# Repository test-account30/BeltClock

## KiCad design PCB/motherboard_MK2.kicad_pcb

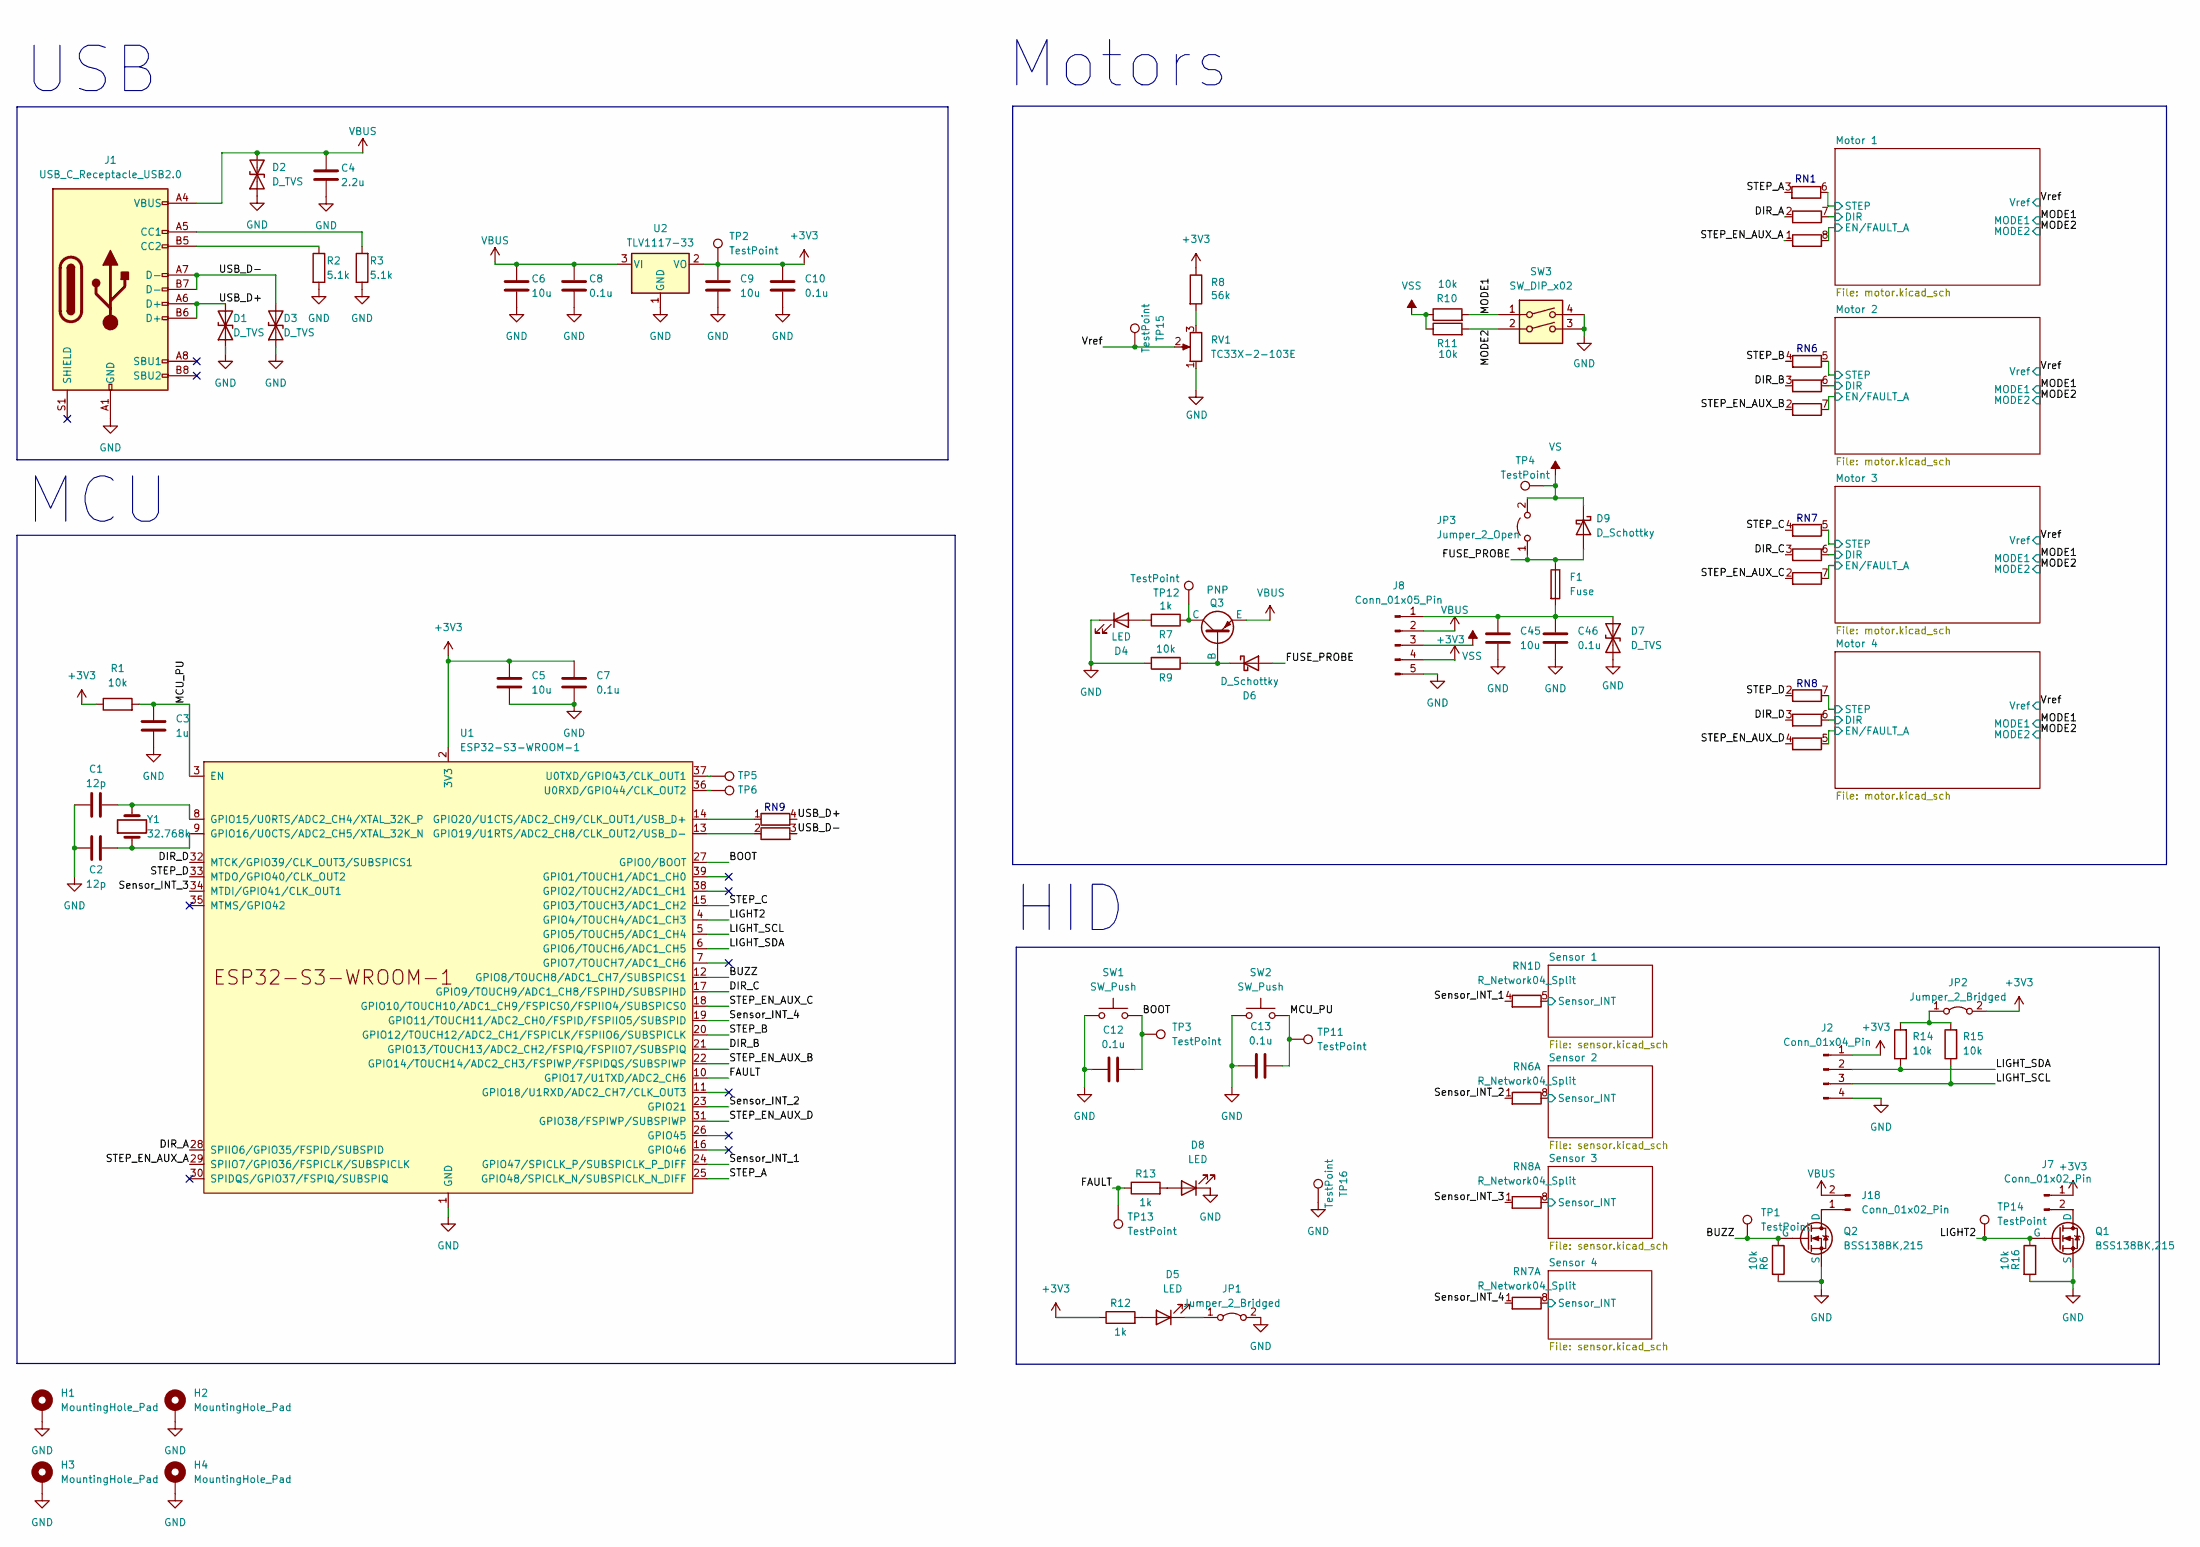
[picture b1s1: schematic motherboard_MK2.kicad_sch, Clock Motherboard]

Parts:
C1, C2: 12p; C_0603_1608Metric; Part Number VJ0805A120FXJCW1BC
C3: 1u; C_0603_1608Metric; Part Number CL10A105KO8NNNC
C4: 2.2u; C_0603_1608Metric; Part Number CL10A225KO8NNNC
C5, C6, C9, C45: 10u; C_1206_3216Metric; Part Number C1206C106K4PACTU
C7, C8, C10, C12, C13, C46: 0.1u; C_0603_1608Metric; Part Number CL10B104KO8NNNC
D1, D3: D_TVS; D_SOD-882; Part Number SP3021-01ETG
D2, D7: D_TVS; ZDO_SOD723_LTF-L; Part Number SP1003-01DTG
D4, D5, D8: LED; LED_0805_2012Metric; Part Number MCL-S270YC
D6: D_Schottky; D_SOD-523; Part Number RB540SM-40FHT2R
D9: D_Schottky; Nexperia_CFP3_SOD-123W; Part Number PMEG4030EXEX
F1: Fuse; Fuse_1206_3216Metric; Part Number F1206FA3000V032TM
H1, H2, H3, H4: MountingHole_Pad; MountingHole_3.2mm_M3; Part Number N/A
J1: USB_C_Receptacle_USB2.0; USB4120-03-C_GCT; Part Number USB4120-03-C
J2: Conn_01x04_Pin; Molex_PicoBlade_53048-0410_1x04_P1.25mm_Horizontal; Part Number 53048-0410
J7: Conn_01x02_Pin; Molex_PicoBlade_53048-0210_1x02_P1.25mm_Horizontal; Part Number 53047-0210
J8: Conn_01x05_Pin; PinHeader_1x05_P2.54mm_Vertical; Part Number generic
J18: Conn_01x02_Pin; Molex_PicoBlade_53047-0210_1x02_P1.25mm_Vertical; Part Number 53047-0210
JP1, JP2: Jumper_2_Bridged; SolderJumper-2_P1.3mm_Bridged2Bar_Pad1.0x1.5mm; Part Number N/A
JP3: Jumper_2_Open; SolderJumper-2_P1.3mm_Open_Pad1.0x1.5mm; Part Number N/A
Q1, Q2: BSS138BK,215; SOT-23; Part Number BSS138BK,215
Q3: PNP; SOT-23; Part Number DSS5240T-7
R1, R6, R10, R11, R14, R15, R16: 10k; R_0603_1608Metric; Part Number MR06X1002FTLV
R2, R3: 5.1k; R_0603_1608Metric; Tolerance 1%; Part Number MCWR06X5101FTL
R7, R12, R13: 1k; R_0805_2012Metric; Tolerence 10%; Part Number MCWR08X1001FTL
R8: 56k; R_0603_1608Metric; Part Number MR06X563 JTLV
R9: 10k; R_0603_1608Metric; Tolerence 10%; Part Number MR06X1002FTLV
RN1, RN6, RN7, RN8: R_Network04_Split; R_Array_Convex_4x0402; Part Number MCPNF42JT-YR0R0
RN9: R_Pack02_Split; R_Array_Convex_2x0402; Part Number MCPNF22JT-YR0R0
RV1: TC33X-2-103E; Potentiometer_Bourns_TC33X_Vertical; Part Number TC33X-2-103E
SW1, SW2: SW_Push; SW_SPST_TL3305A; Part Number TL3305AF160QG.
SW3: SW_DIP_x02; DIP-4_W7.62mm; Part Number MCNDI-02S
TP1, TP3, TP11, TP12, TP13, TP14: TestPoint; TestPoint_Pad_D1.0mm; Part Number N/A
TP2, TP4, TP5, TP6, TP16: TestPoint; TestPoint_Pad_1.0x1.0mm; Part Number N/A
TP15: TestPoint; TestPoint_Pad_2.0x2.0mm; Part Number N/A
U1: ESP32-S3-WROOM-1; Part Number DFR0896
U2: TLV1117-33; SOT-223; Part Number LD1117S33CTR
Y1: 32.768k; Crystal_SMD_3215-2Pin_3.2x1.5mm; Part Number RT3215-32.768-12.5-TR-10PPM

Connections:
+3V3: C5.1, C7.1, C9.1, C10.1, J2.1, J7.1, J8.4, JP2.2 (B), R1.1, R8.1, R12.1, TP2.1, U1.2 (3V3), U2.2 (VO); also elsewhere on the board
/BOOT: C12.1, SW1.2, TP3.1, U1.27 (GPIO0/BOOT)
/BUZZ: Q2.2 (G), R6.1, TP1.1, U1.12 (GPIO8/TOUCH8/ADC1_CH7/SUBSPICS1)
/DIR_A: RN1.2, U1.28 (SPIIO6/GPIO35/FSPID/SUBSPID)
/DIR_B: RN6.3, U1.21 (GPIO13/TOUCH13/ADC2_CH2/FSPIQ/FSPIIO7/S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)
/DIR_C: RN7.3, U1.17 (GPIO9/TOUCH9/ADC1_CH8/FSPIHD/SUBSPIHD)
/DIR_D: RN8.3, U1.32 (MTCK/GPIO39/CLK_OUT3/SUBSPICS1)
/FAULT: R13.1, TP13.1, U1.10 (GPIO17/U1TXD/ADC2_CH6)
/FUSE_PROBE: D6.2 (A), D9.2 (A), F1.1, JP3.1 (A)
/LIGHT2: Q1.2 (G), R16.1, TP14.1, U1.4 (GPIO4/TOUCH4/ADC1_CH3)
/LIGHT_SCL: J2.3, R15.1, U1.5 (GPIO5/TOUCH5/ADC1_CH4)
/LIGHT_SDA: J2.2, R14.1, U1.6 (GPIO6/TOUCH6/ADC1_CH5)
/MCU_PU: C3.1, C13.1, R1.2, SW2.2, TP11.1, U1.3 (EN)
/MODE1: R10.2, SW3.1; also elsewhere on the board
/MODE2: R11.2, SW3.2; also elsewhere on the board
/Motor 1/DIR: RN1.7; also elsewhere on the board
/Motor 1/EN/FAULT: RN1.8; also elsewhere on the board
/Motor 1/STEP: RN1.6; also elsewhere on the board
/Motor 2/DIR: RN6.6; also elsewhere on the board
/Motor 2/EN/FAULT: RN6.7; also elsewhere on the board
/Motor 2/STEP: RN6.5; also elsewhere on the board
/Motor 3/DIR: RN7.6; also elsewhere on the board
/Motor 3/EN/FAULT: RN7.7; also elsewhere on the board
/Motor 3/STEP: RN7.5; also elsewhere on the board
/Motor 4/DIR: RN8.6; also elsewhere on the board
/Motor 4/EN/FAULT: RN8.5; also elsewhere on the board
/Motor 4/STEP: RN8.7; also elsewhere on the board
/STEP_A: RN1.3, U1.25 (GPIO48/SPICLK_N/SUBSPICLK_N_DIFF)
/STEP_B: RN6.4, U1.20 (GPIO12/TOUCH12/ADC2_CH1/FSPICLK/FSPIIO6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)
/STEP_C: RN7.4, U1.15 (GPIO3/TOUCH3/ADC1_CH2)
/STEP_D: RN8.2, U1.33 (MTDO/GPIO40/CLK_OUT2)
/STEP_EN_AUX_A: RN1.1, U1.29 (SPIIO7/GPIO36/FSPICLK/SUBSPICLK)
/STEP_EN_AUX_B: RN6.2, U1.22 (GPIO14/TOUCH14/ADC2_CH3/FSPIWP/FSPIDQS/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)
/STEP_EN_AUX_C: RN7.2, U1.18 (GPIO10/TOUCH10/ADC1_CH9/FSPICS0/FSPIIO4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)
/STEP_EN_AUX_D: RN8.4, U1.31 (GPIO38/FSPIWP/SUBSPIWP)
/Sensor 1/Sensor_INT: RN1.5; also elsewhere on the board
/Sensor 2/Sensor_INT: RN6.8; also elsewhere on the board
/Sensor 3/Sensor_INT: RN8.8; also elsewhere on the board
/Sensor 4/Sensor_INT: RN7.8; also elsewhere on the board
/Sensor_INT_1: RN1.4, U1.24 (GPIO47/SPICLK_P/SUBSPICLK_P_DIFF)
/Sensor_INT_2: RN6.1, U1.23 (GPIO21)
/Sensor_INT_3: RN8.1, U1.34 (MTDI/GPIO41/CLK_OUT1)
/Sensor_INT_4: RN7.1, U1.19 (GPIO11/TOUCH11/ADC2_CH0/FSPID/FSPIIO5/S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)
/USB_D+: D1.2 (A2), J1.A6 (D+), J1.B6 (D+), RN9.4 (R1.2)
/USB_D-: D3.2 (A2), J1.A7 (D-), J1.B7 (D-), RN9.3 (R2.2)
/Vref: RV1.2, TP15.1; also elsewhere on the board
GND: C1.1, C2.1, C3.2, C4.2, C5.2, C6.2, C7.2, C8.2, C9.2, C10.2, C12.2, C13.2, C45.2, C46.2, D1.1 (A1), D2.1 (A1), D3.1 (A1), D4.1 (K), D7.2 (A2), D8.1 (K), H1.1, H2.1, H3.1, H4.1, J1.A1 (GND), J1.A12 (GND), J1.B1 (GND), J1.B12 (GND), J2.4, J8.5, JP1.2 (B), Q1.3 (S), Q2.3 (S), R2.2, R3.1, R6.2, R9.2, R16.2, RV1.1, SW1.1, SW2.1, SW3.3, SW3.4, TP16.1, U1.1 (GND), U1.40 (GND), U1.41 (GND), U2.1 (GND); also elsewhere on the board
unnamed: D4.2 (A), R7.2
unnamed: D5.2 (A), R12.2
unnamed: D5.1 (K), JP1.1 (A)
unnamed: D6.1 (K), Q3.2 (B), R9.1
unnamed: C45.1, C46.1, D7.1 (A1), F1.2, J8.1
unnamed: D8.2 (A), R13.2
unnamed: J1.A5 (CC1), R3.2
unnamed: J1.B5 (CC2), R2.1
unnamed: J7.2, Q1.1 (D)
unnamed: J18.1, Q2.1 (D)
unnamed: JP2.1 (A), R14.2, R15.2
unnamed: Q3.1 (C), R7.1, TP12.1
unnamed: R8.2, RV1.3
unnamed: RN9.1 (R1.1), U1.14 (GPIO20/U1CTS/ADC2_CH9/CLK_OUT1/USB_D+)
unnamed: RN9.2 (R2.1), U1.13 (GPIO19/U1RTS/ADC2_CH8/CLK_OUT2/USB_D-)
unnamed: C1.2, U1.8 (GPIO15/U0RTS/ADC2_CH4/XTAL_32K_P), Y1.2
unnamed: C2.2, U1.9 (GPIO16/U0CTS/ADC2_CH5/XTAL_32K_N), Y1.1
unnamed: TP6.1, U1.36 (U0RXD/GPIO44/CLK_OUT2)
unnamed: TP5.1, U1.37 (U0TXD/GPIO43/CLK_OUT1)
VBUS: C4.1, C6.1, C8.1, D2.2 (A2), J1.A4 (VBUS), J1.A9 (VBUS), J1.B4 (VBUS), J1.B9 (VBUS), J8.2, J18.2, Q3.3 (E), U2.3 (VI)
VS: D9.1 (K), JP3.2 (B), TP4.1; also elsewhere on the board
VSS: J8.3, R10.1, R11.1; also elsewhere on the board

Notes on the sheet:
RN6
HID
USB
Motors
RN9
RN8
RN1
RN7
MCU

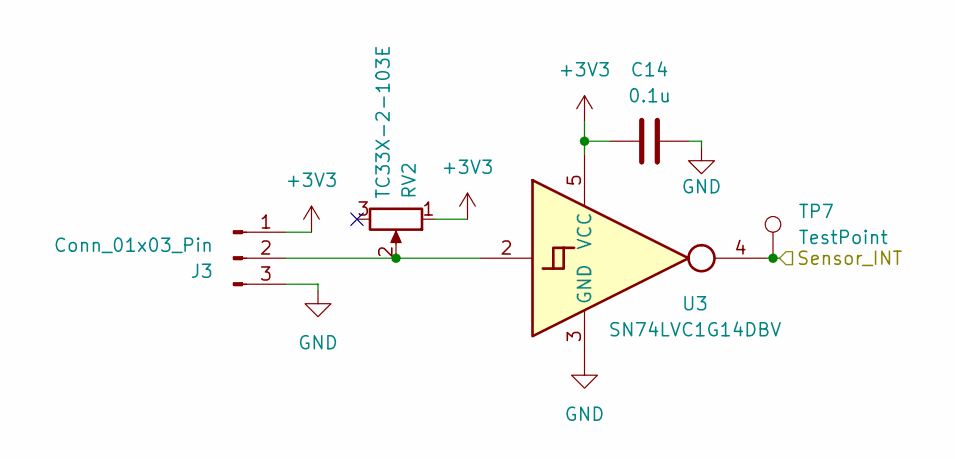
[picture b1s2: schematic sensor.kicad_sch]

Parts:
C14: 0.1u; C_0603_1608Metric; Part Number CL10B104KO8NNNC
J3: Conn_01x03_Pin; Molex_PicoBlade_53048-0310_1x03_P1.25mm_Horizontal; Part Number 53048-0310
RV2: TC33X-2-103E; Potentiometer_Bourns_TC33X_Vertical; Part Number TC33X-2-103E
TP7: TestPoint; TestPoint_Pad_D1.0mm; Part Number N/A
U3: SN74LVC1G14DBV; SC-74A-5_1.55x2.9mm_P0.95mm; Part Number 74LVC1G14GW-Q100,1

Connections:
+3V3: C14.1, J3.1, RV2.1, U3.5 (VCC); also elsewhere on the board
/Sensor 1/Sensor_INT: TP7.1, U3.4; also elsewhere on the board
GND: C14.2, J3.3, U3.3 (GND); also elsewhere on the board
unnamed: J3.2, RV2.2, U3.2

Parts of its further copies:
C40, C41, C42: 0.1u; C_0603_1608Metric; Part Number CL10B104KO8NNNC
J4, J5, J6: Conn_01x03_Pin; Molex_PicoBlade_53048-0310_1x03_P1.25mm_Horizontal; Part Number 53048-0310
RV3, RV4, RV5: TC33X-2-103E; Potentiometer_Bourns_TC33X_Vertical; Part Number TC33X-2-103E
TP8, TP9, TP10: TestPoint; TestPoint_Pad_D1.0mm; Part Number N/A
U9, U10, U11: SN74LVC1G14DBV; SC-74A-5_1.55x2.9mm_P0.95mm; Part Number 74LVC1G14GW-Q100,1

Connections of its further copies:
+3V3: C40.1, C41.1, C42.1, J4.1, J5.1, J6.1, RV3.1, RV4.1, RV5.1, U9.5 (VCC), U10.5 (VCC), U11.5 (VCC); also elsewhere on the board
/Sensor 2/Sensor_INT: TP8.1, U9.4; also elsewhere on the board
/Sensor 3/Sensor_INT: TP9.1, U10.4; also elsewhere on the board
/Sensor 4/Sensor_INT: TP10.1, U11.4; also elsewhere on the board
GND: C40.2, C41.2, C42.2, J4.3, J5.3, J6.3, U9.3 (GND), U10.3 (GND), U11.3 (GND); also elsewhere on the board
unnamed: J4.2, RV3.2, U9.2
unnamed: J5.2, RV4.2, U10.2
unnamed: J6.2, RV5.2, U11.2

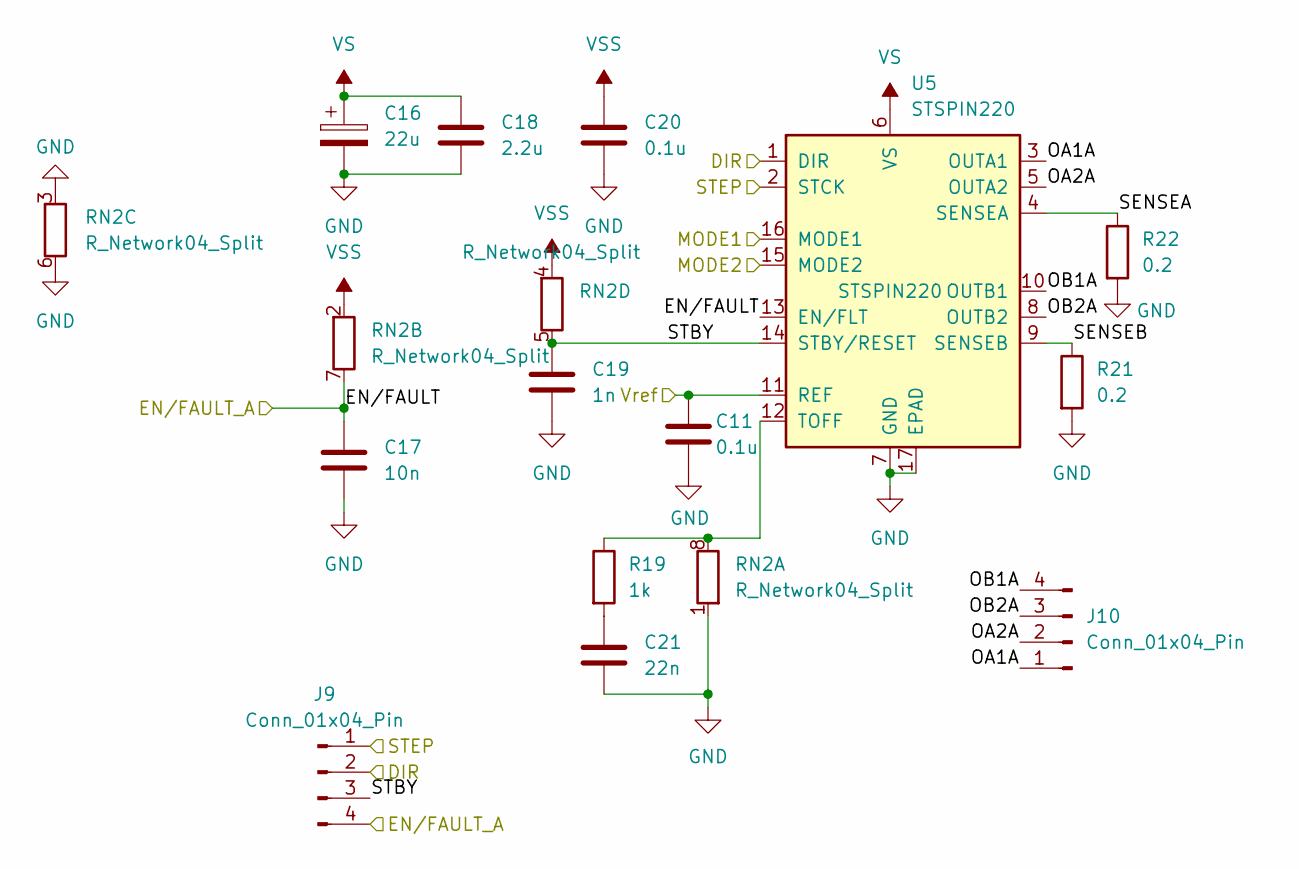
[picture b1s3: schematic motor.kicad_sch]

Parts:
C11, C20: 0.1u; C_0603_1608Metric; Part Number CL10B104KO8NNNC
C16: 22u; CP_Elec_5x5.4; Part Number MCVVT016M220DA1L
C17: 10n; C_0603_1608Metric; Part Number MC0603B103K160CT
C18: 2.2u; C_0603_1608Metric; Part Number CL10A225KO8NNNC
C19: 1n; C_0603_1608Metric; Part Number CC0603KRX7R7BB102
C21: 22n; C_0603_1608Metric; Part Number KGM15AR71C222KT
J9: Conn_01x04_Pin; PinHeader_1x04_P2.54mm_Vertical; Part Number generic
J10: Conn_01x04_Pin; Molex_PicoBlade_53048-0410_1x04_P1.25mm_Horizontal; Part Number 53048-0410
R19: 1k; R_0603_1608Metric; Part Number MR06X1001FTLV
R21, R22: 0.2; R_0805_2012Metric; Part Number WW08WR200FTL
RN2: R_Network04_Split; R_Array_Convex_4x0603; Part Number WA06X103 JTL
U5: STSPIN220; VQFN-16-1EP_3x3mm_P0.5mm_EP1.8x1.8mm_ThermalVias; Part Number STSPIN220

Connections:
/MODE1: U5.16 (MODE1); also elsewhere on the board
/MODE2: U5.15 (MODE2); also elsewhere on the board
/Motor 1/DIR: J9.2, U5.1 (DIR); also elsewhere on the board
/Motor 1/EN/FAULT: C17.1, J9.4, RN2.7, U5.13 (EN/FLT); also elsewhere on the board
/Motor 1/OA1A: J10.1, U5.3 (OUTA1)
/Motor 1/OA2A: J10.2, U5.5 (OUTA2)
/Motor 1/OB1A: J10.4, U5.10 (OUTB1)
/Motor 1/OB2A: J10.3, U5.8 (OUTB2)
/Motor 1/SENSEA: R22.1, U5.4 (SENSEA)
/Motor 1/SENSEB: R21.1, U5.9 (SENSEB)
/Motor 1/STBY: C19.1, J9.3, RN2.5, U5.14 (STBY/RESET)
/Motor 1/STEP: J9.1, U5.2 (STCK); also elsewhere on the board
/Vref: C11.1, U5.11 (REF); also elsewhere on the board
GND: C11.2, C16.2, C17.2, C18.2, C19.2, C20.2, C21.2, R21.2, R22.2, RN2.1, RN2.3, RN2.6, U5.7 (GND), U5.17 (EPAD); also elsewhere on the board
unnamed: C21.1, R19.2
unnamed: R19.1, RN2.8, U5.12 (TOFF)
VS: C16.1, C18.1, U5.6 (VS); also elsewhere on the board
VSS: C20.1, RN2.2, RN2.4; also elsewhere on the board

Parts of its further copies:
C15, C26, C32, C38, C43, C44: 0.1u; C_0603_1608Metric; Part Number CL10B104KO8NNNC
C22, C28, C34: 22u; CP_Elec_5x5.4; Part Number MCVVT016M220DA1L
C23, C29, C35: 10n; C_0603_1608Metric; Part Number MC0603B103K160CT
C24, C30, C36: 2.2u; C_0603_1608Metric; Part Number CL10A225KO8NNNC
C25, C31, C37: 1n; C_0603_1608Metric; Part Number CC0603KRX7R7BB102
C27, C33, C39: 22n; C_0603_1608Metric; Part Number KGM15AR71C222KT
J11, J13, J15: Conn_01x04_Pin; PinHeader_1x04_P2.54mm_Vertical; Part Number generic
J12, J14, J16: Conn_01x04_Pin; Molex_PicoBlade_53048-0410_1x04_P1.25mm_Horizontal; Part Number 53048-0410
R25, R31, R37: 1k; R_0603_1608Metric; Part Number MR06X1001FTLV
R27, R28, R33, R34, R39, R40: 0.2; R_0805_2012Metric; Part Number WW08WR200FTL
RN3, RN4, RN5: R_Network04_Split; R_Array_Convex_4x0603; Part Number WA06X103 JTL
U6, U7, U8: STSPIN220; VQFN-16-1EP_3x3mm_P0.5mm_EP1.8x1.8mm_ThermalVias; Part Number STSPIN220

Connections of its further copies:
/MODE1: U6.16 (MODE1), U7.16 (MODE1), U8.16 (MODE1); also elsewhere on the board
/MODE2: U6.15 (MODE2), U7.15 (MODE2), U8.15 (MODE2); also elsewhere on the board
/Motor 2/DIR: J11.2, U6.1 (DIR); also elsewhere on the board
/Motor 2/EN/FAULT: C23.1, J11.4, RN3.7, U6.13 (EN/FLT); also elsewhere on the board
/Motor 2/OA1A: J12.1, U6.3 (OUTA1)
/Motor 2/OA2A: J12.2, U6.5 (OUTA2)
/Motor 2/OB1A: J12.4, U6.10 (OUTB1)
/Motor 2/OB2A: J12.3, U6.8 (OUTB2)
/Motor 2/SENSEA: R28.1, U6.4 (SENSEA)
/Motor 2/SENSEB: R27.1, U6.9 (SENSEB)
/Motor 2/STBY: C25.1, J11.3, RN3.5, U6.14 (STBY/RESET)
/Motor 2/STEP: J11.1, U6.2 (STCK); also elsewhere on the board
/Motor 3/DIR: J13.2, U7.1 (DIR); also elsewhere on the board
/Motor 3/EN/FAULT: C29.1, J13.4, RN4.7, U7.13 (EN/FLT); also elsewhere on the board
/Motor 3/OA1A: J14.1, U7.3 (OUTA1)
/Motor 3/OA2A: J14.2, U7.5 (OUTA2)
/Motor 3/OB1A: J14.4, U7.10 (OUTB1)
/Motor 3/OB2A: J14.3, U7.8 (OUTB2)
/Motor 3/SENSEA: R34.1, U7.4 (SENSEA)
/Motor 3/SENSEB: R33.1, U7.9 (SENSEB)
/Motor 3/STBY: C31.1, J13.3, RN4.5, U7.14 (STBY/RESET)
/Motor 3/STEP: J13.1, U7.2 (STCK); also elsewhere on the board
/Motor 4/DIR: J15.2, U8.1 (DIR); also elsewhere on the board
/Motor 4/EN/FAULT: C35.1, J15.4, RN5.7, U8.13 (EN/FLT); also elsewhere on the board
/Motor 4/OA1A: J16.1, U8.3 (OUTA1)
/Motor 4/OA2A: J16.2, U8.5 (OUTA2)
/Motor 4/OB1A: J16.4, U8.10 (OUTB1)
/Motor 4/OB2A: J16.3, U8.8 (OUTB2)
/Motor 4/SENSEA: R40.1, U8.4 (SENSEA)
/Motor 4/SENSEB: R39.1, U8.9 (SENSEB)
/Motor 4/STBY: C37.1, J15.3, RN5.5, U8.14 (STBY/RESET)
/Motor 4/STEP: J15.1, U8.2 (STCK); also elsewhere on the board
/Vref: C15.1, C43.1, C44.1, U6.11 (REF), U7.11 (REF), U8.11 (REF); also elsewhere on the board
GND: C15.2, C22.2, C23.2, C24.2, C25.2, C26.2, C27.2, C28.2, C29.2, C30.2, C31.2, C32.2, C33.2, C34.2, C35.2, C36.2, C37.2, C38.2, C39.2, C43.2, C44.2, R27.2, R28.2, R33.2, R34.2, R39.2, R40.2, RN3.1, RN3.3, RN3.6, RN4.1, RN4.3, RN4.6, RN5.1, RN5.3, RN5.6, U6.7 (GND), U6.17 (EPAD), U7.7 (GND), U7.17 (EPAD), U8.7 (GND), U8.17 (EPAD); also elsewhere on the board
unnamed: C27.1, R25.2
unnamed: C33.1, R31.2
unnamed: C39.1, R37.2
unnamed: R25.1, RN3.8, U6.12 (TOFF)
unnamed: R31.1, RN4.8, U7.12 (TOFF)
unnamed: R37.1, RN5.8, U8.12 (TOFF)
VS: C22.1, C24.1, C28.1, C30.1, C34.1, C36.1, U6.6 (VS), U7.6 (VS), U8.6 (VS); also elsewhere on the board
VSS: C26.1, C32.1, C38.1, RN3.2, RN3.4, RN4.2, RN4.4, RN5.2, RN5.4; also elsewhere on the board

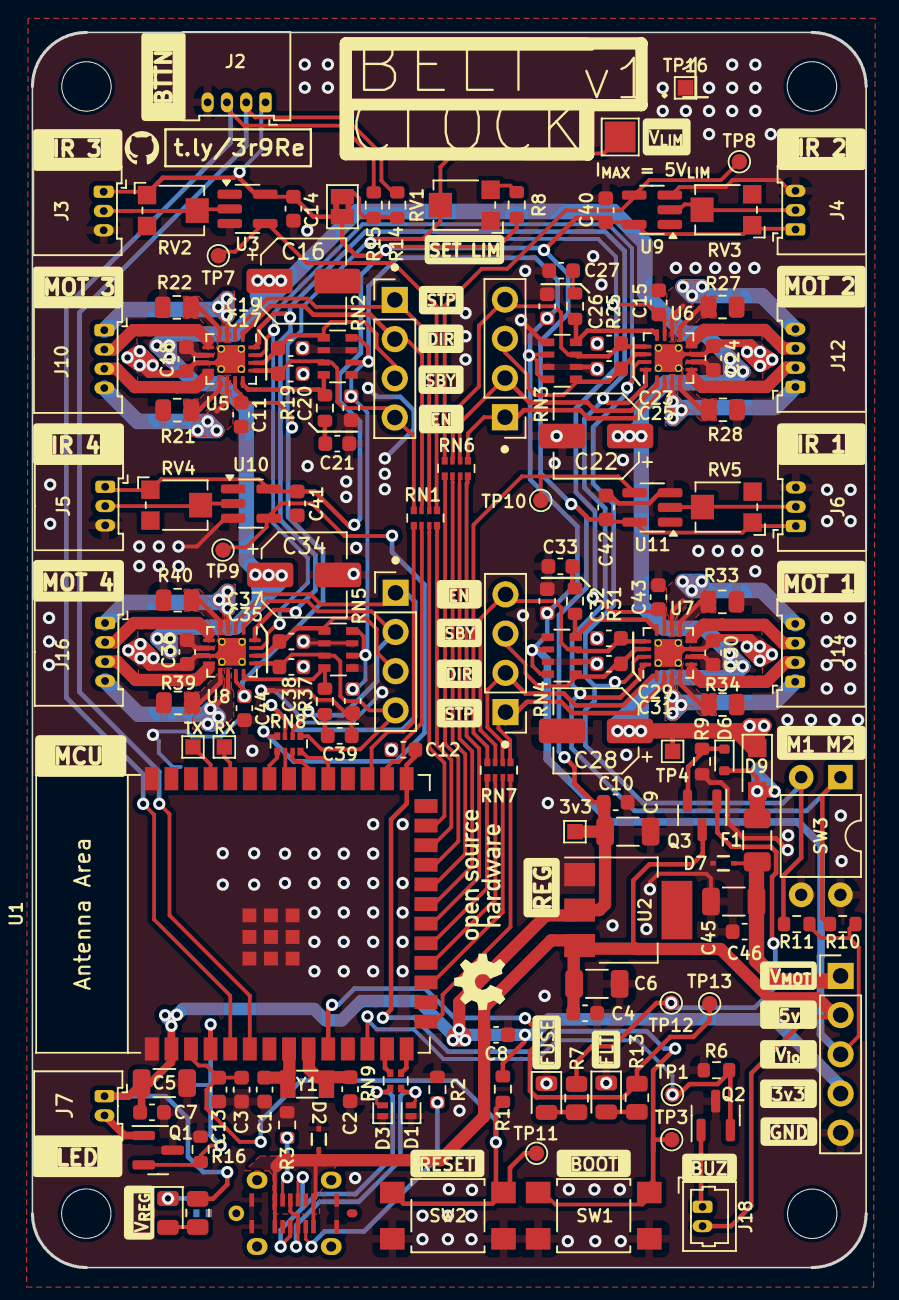
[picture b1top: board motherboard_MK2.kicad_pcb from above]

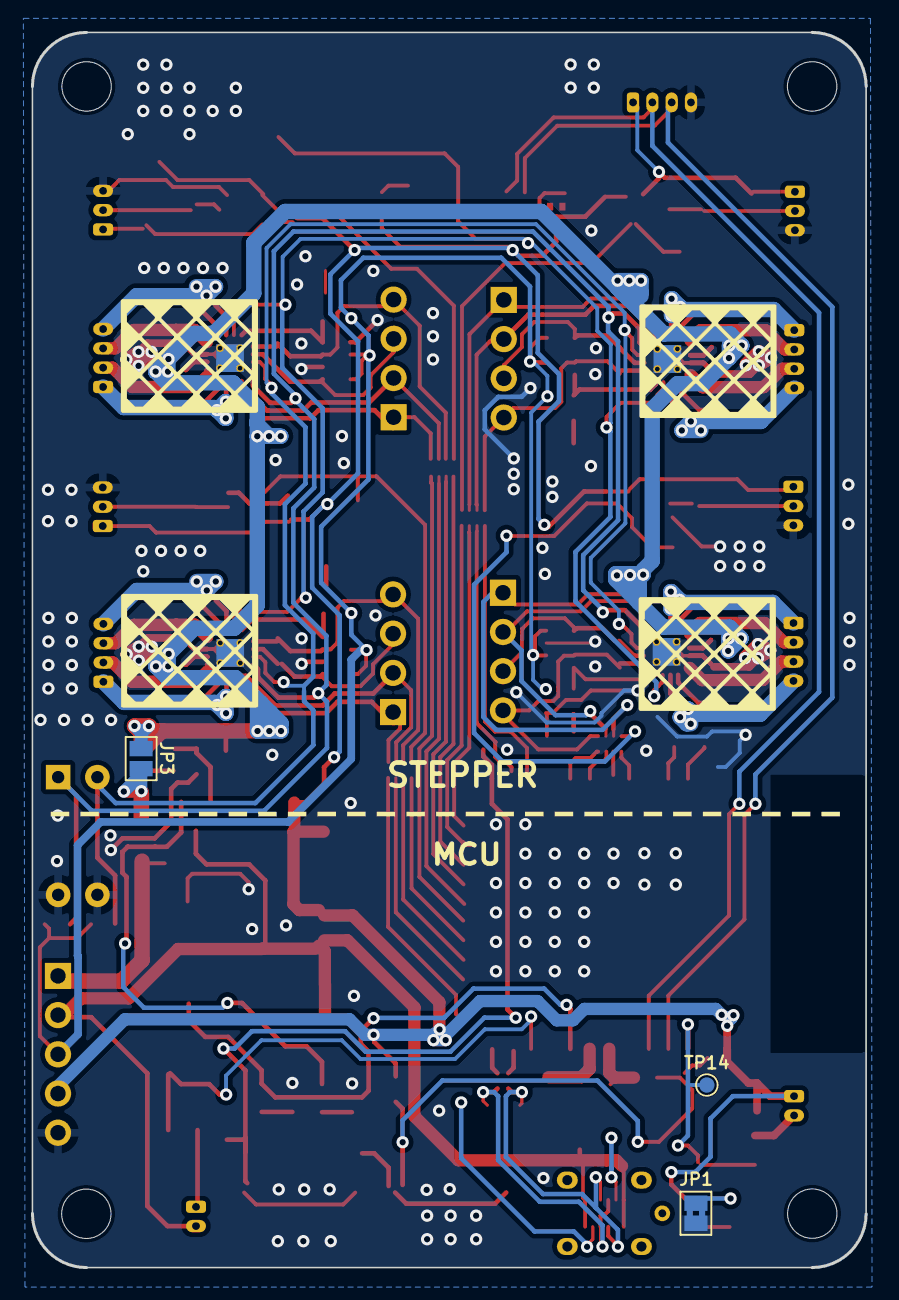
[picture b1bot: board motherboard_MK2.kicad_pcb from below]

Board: 2 copper layers, 54.0 x 80.0 mm, 153 parts (3 on the bottom side), 109 nets.

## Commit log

2025-01-04 Init
2025-01-04 Rename Board/motherboard.kicad_pro to PCB/Board/motherboard.kicad_pro
2025-01-04 Rename Schematic/motherboard.pdf to PCB/Schematic/motherboard.pdf
